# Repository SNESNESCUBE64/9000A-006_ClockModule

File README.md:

# 9000A-006_ClockModule
Reproduction Fluke 9000a Async clock module for Fluke 9010a devices with option 006

*design has not been completely tested, however it follows the original design schematics*

The cable used to hook up the module to the 9010 is just a DB15 male to DB15 male.

Front:  

Back:

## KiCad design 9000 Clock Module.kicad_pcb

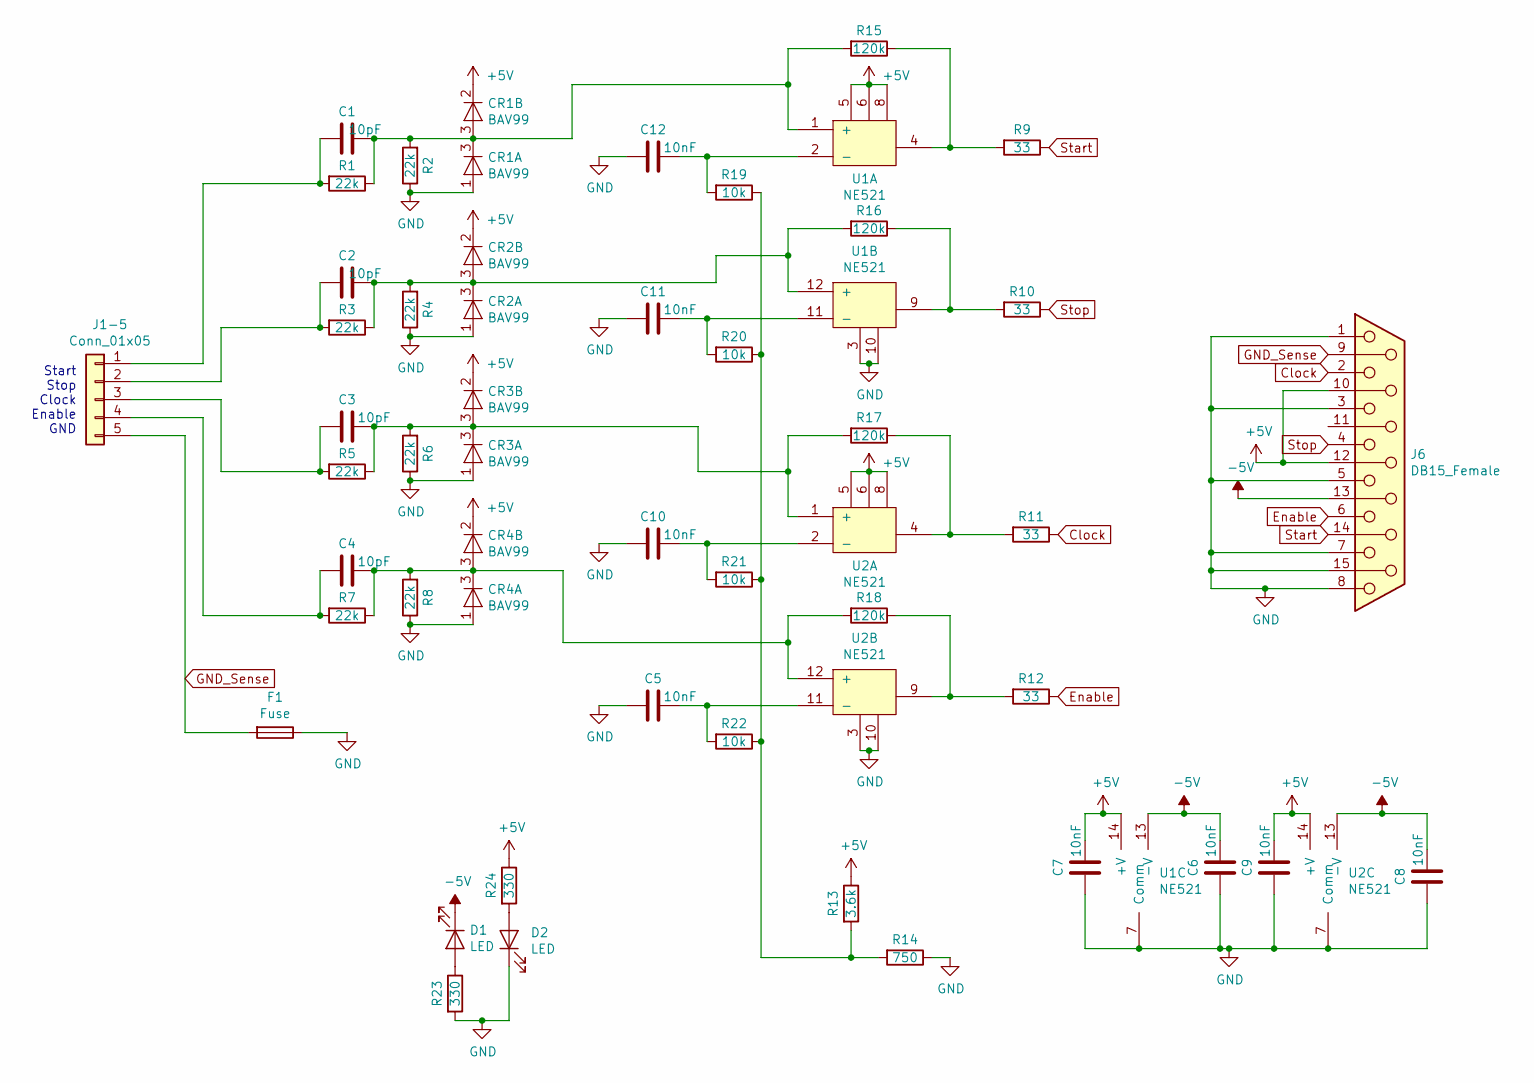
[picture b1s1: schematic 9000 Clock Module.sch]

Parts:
C1, C2, C3, C4: 10pF; R_0603_HandSoldering
C5, C6, C7, C8, C9, C10, C11, C12: 10nF; R_0603_HandSoldering
CR1, CR2, CR3, CR4: BAV99; SOT-23
D1, D2: LED; LED_0603_HandSoldering
F1: Fuse; Fuseholder5x20_horiz_open_inline_Type-I
J1-5: Conn_01x05; Pin_Header_Straight_1x05_Pitch2.54mm
J6: DB15_Female; DSUB-15_Female_Horizontal_P2.77x2.84mm_EdgePinOffset7.70mm_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
R1, R2, R3, R4, R5, R6, R7, R8: 22k; R_0603_HandSoldering
R9, R10, R11, R12: 33; R_0603_HandSoldering
R13: 3.6k; R_0603_HandSoldering
R14: 750; R_0603_HandSoldering
R15, R16, R17, R18: 120k; R_0603_HandSoldering
R19, R20, R21, R22: 10k; R_0603_HandSoldering
R23, R24: 330; R_0603_HandSoldering
U1, U2: NE521; SOIC-14_3.9x8.7mm_Pitch1.27mm

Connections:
+5V: C7.1, C9.1, CR1.2 (K), CR2.2 (K), CR3.2 (K), CR4.2 (K), J6.10, J6.12, R13.1, R24.1, U1.5, U1.6, U1.8, U1.14 (+V), U2.5, U2.6, U2.8, U2.14 (+V)
-5V: C6.1, C8.1, D1.1 (K), J6.13, U1.13 (-V), U2.13 (-V)
Clock: J6.2, R11.1
Enable: J6.6, R12.1
GND: C5.2, C6.2, C7.2, C8.2, C9.2, C10.2, C11.2, C12.2, CR1.1 (A), CR2.1 (A), CR3.1 (A), CR4.1 (A), D2.1 (K), F1.1, J6.0, J6.1, J6.3, J6.5, J6.7, J6.8, J6.15, R2.1, R4.1, R6.1, R8.1, R14.1, R23.2, U1.3, U1.7 (Comm), U1.10, U2.3, U2.7 (Comm), U2.10
GND_Sense: F1.2, J1-5.5, J6.9
unnamed: C1.1, CR1.3 (K), R1.1, R2.2, R15.2, U1.1 (+)
unnamed: C1.2, J1-5.1, R1.2
unnamed: C2.1, CR2.3 (K), R3.1, R4.2, R16.2, U1.12 (+)
unnamed: C2.2, J1-5.2, R3.2
unnamed: C3.1, CR3.3 (K), R5.1, R6.2, R17.2, U2.1 (+)
unnamed: C3.2, J1-5.3, R5.2
unnamed: C4.1, CR4.3 (K), R7.1, R8.2, R18.2, U2.12 (+)
unnamed: C4.2, J1-5.4, R7.2
unnamed: C5.1, R22.2, U2.11 (-)
unnamed: C10.1, R21.2, U2.2 (-)
unnamed: C11.1, R20.2, U1.11 (-)
unnamed: C12.1, R19.2, U1.2 (-)
unnamed: D1.2 (A), R23.1
unnamed: D2.2 (A), R24.2
unnamed: R10.2, R16.1, U1.9
unnamed: R11.2, R17.1, U2.4
unnamed: R12.2, R18.1, U2.9
unnamed: R13.2, R14.2, R19.1, R20.1, R21.1, R22.1
unnamed: R9.2, R15.1, U1.4
Start: J6.14, R9.1
Stop: J6.4, R10.1

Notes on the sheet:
Start Stop Clock Enable GND

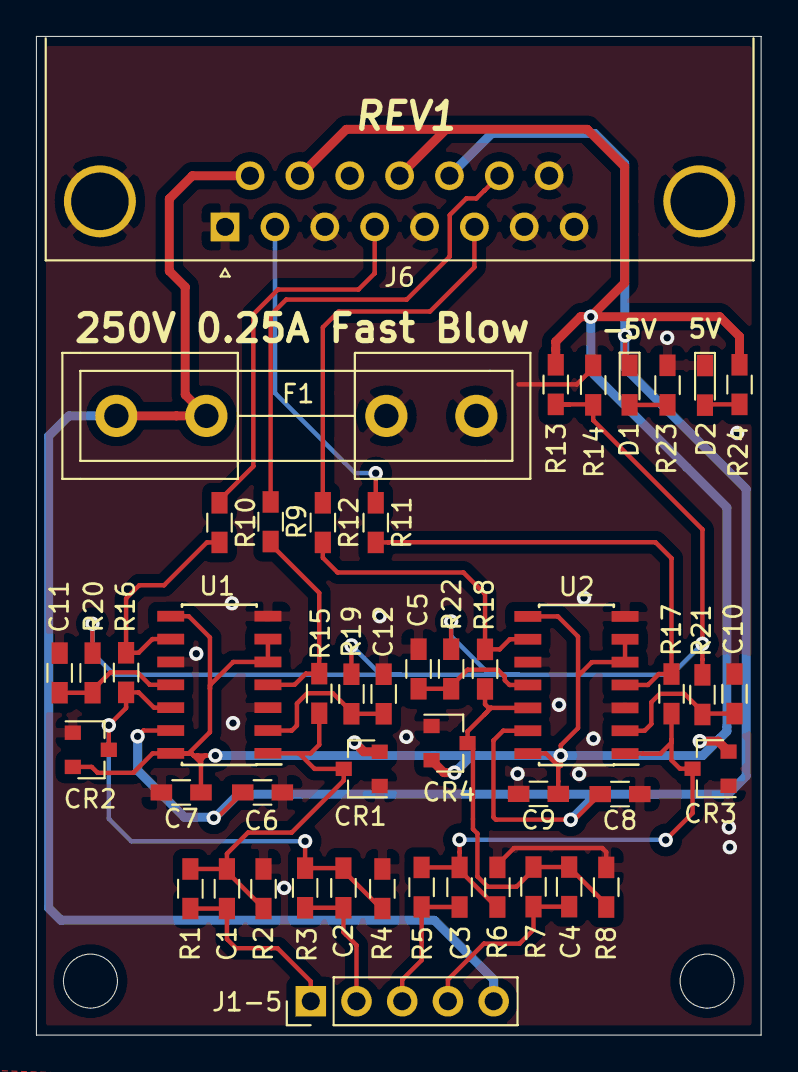
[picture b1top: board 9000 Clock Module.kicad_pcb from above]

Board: 2 copper layers, 40.3 x 55.5 mm, 47 parts (0 on the bottom side), 27 nets.

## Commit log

2021-07-27 Added module design
